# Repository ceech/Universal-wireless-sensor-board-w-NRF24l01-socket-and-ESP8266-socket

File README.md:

# Universal-wireless-sensor-board-w-NRF24l01-socket-and-ESP8266-socket
These are the CadsoftEagle board and schematic files. Link to the schematic:
http://s1164.photobucket.com/user/ceech123/media/DbALMmf_zpsipenpm1w.png.html

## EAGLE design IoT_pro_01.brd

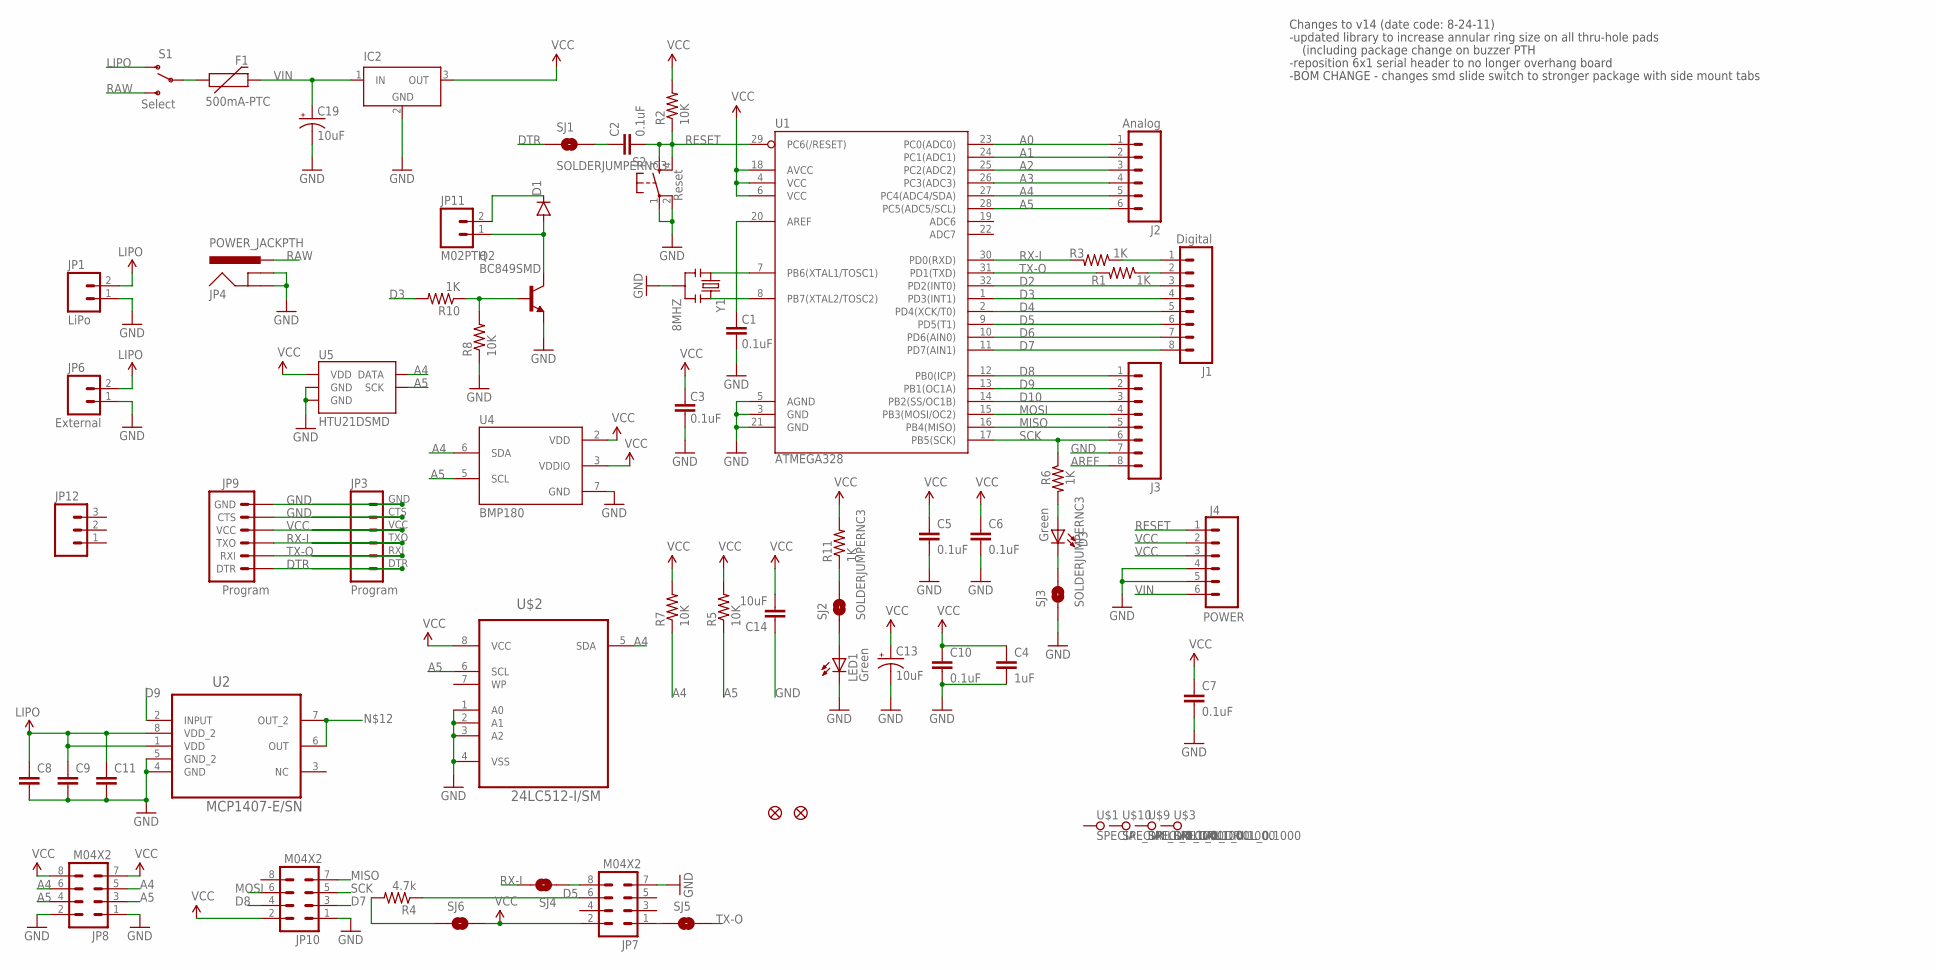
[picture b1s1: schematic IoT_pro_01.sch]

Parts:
C1, C2, C3, C5, C6, C7, C10: 0.1uF; 0805
C4: 1uF; 0805
C8, C9, C11: CAP0805; 0805
C13, C19: 10uF; EIA3216
C14: 10uF; 0805
D1: DIODESOD; SOD-323
D3: Green; PLCC2
F1: 500mA-PTC; PTC-1206
IC2: LT1129CST5; SOT223
J1: Digital; 1X08
J2: Analog; 1X06
J3: M081X08; 1X08
J4: POWER; 1X06
JP1: LiPo; MOLEX-1X2
JP2, JP5: FIDUCIAL1X2.5; FIDUCIAL-1X2.5
JP3: Program; 1X06
JP4: POWER_JACKPTH; POWER_JACK_PTH
JP6: External; 1X02
JP7, JP8, JP10: M04X2; 2X4
JP9: Program; 1X06-SMD
JP11: M02PTH; 1X02
JP12: M03PTH; 1X03
LED1: Green; PLCC2
Q2: BC849SMD; SOT23-BEC
R1, R3, R6, R10, R11: 1K; 0805
R2, R5, R7, R8: 10K; 0805
R4: 4.7k; 0805
S1: Select; SWITCH-SPST-SMD-A
S2: Reset; TACTILE_SWITCH_SMD
SJ1, SJ2, SJ3: SOLDERJUMPERNC3; SJ_2S-NOTRACE
SJ4, SJ5, SJ6: SOLDERJUMPERNC2; SJ_2S-NOTRACE
U1: ATMEGA328; TQFP32-08
U2: MCP1407-E/SN; SOIC127P600X175-8N
U4: BMP180
U5: HTU21DSMD; HTU21D
U$1, U$3, U$9, U$10: SPECIAL_DRILL_0.1000; PAD_0.1000
U$2: 24LC512-I/SM; SOIC127P794X203-8N
Y1: 8MHZ; RESONATOR-SMD

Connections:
3.3V: C8.1, C9.1, C11.1, JP6.2, U2.1 (VDD), U2.8 (VDD_2)
A0: J2.1, U1.23 (PC0(ADC0))
A1: J2.2, U1.24 (PC1(ADC1))
A2: J2.3, U1.25 (PC2(ADC2))
A3: J2.4, U1.26 (PC3(ADC3))
A4: J2.5, JP8.5, JP8.6, R7.1, U1.27 (PC4(ADC4/SDA)), U4.6 (SDA), U5.DATA, U$2.5 (SDA)
A5: J2.6, JP8.3, JP8.4, R5.1, U1.28 (PC5(ADC5/SCL)), U4.5 (SCL), U5.SCK, U$2.6 (SCL)
AREF: C1.2, J3.8, U1.20 (AREF)
D2: J1.3, U1.32 (PD2(INT0))
D3: J1.4, R10.2, U1.1 (PD3(INT1))
D4: J1.5, U1.2 (PD4(XCK/T0))
D5: J1.6, JP7.6, R4.1, U1.9 (PD5(T1))
D6: J1.7, U1.10 (PD6(AIN0))
D7: J1.8, JP10.3, U1.11 (PD7(AIN1))
D8: J3.1, JP10.4, U1.12 (PB0(ICP))
D9: J3.2, U1.13 (PB1(OC1A)), U2.2 (INPUT)
D10: J3.3, U1.14 (PB2(SS/OC1B))
DTR: JP3.DTR (1), JP9.1 (DTR), SJ1.1
GND: C1.1, C3.1, C4.2, C5.2, C6.2, C7.2, C8.2, C9.2, C10.2, C11.2, C13.C (-), C14.1, C19.C (-), IC2.2 (GND), IC2.4 (GND), J3.7, J4.4, J4.5, JP1.1, JP3.CTS (5), JP3.GND (6), JP4.GND, JP4.GNDBREAK, JP6.1, JP7.7, JP8.1, JP8.2, JP9.5 (CTS), JP9.6 (GND), JP10.1, LED1.C, Q2.E, R8.1, S2.1, S2.2, SJ3.1, U1.3 (GND), U1.5 (AGND), U1.21 (GND), U2.4 (GND), U2.5 (GND_2), U4.7 (GND), U5.7 (GND), U5.GND, U$2.1 (A0), U$2.2 (A1), U$2.3 (A2), U$2.4 (VSS), Y1.2
LIPO: JP1.2, S1.1 (O)
MISO: J3.5, JP10.7, U1.16 (PB4(MISO))
MOSI: J3.4, JP10.6, U1.15 (PB3(MOSI/OC2))
unnamed: C2.1, SJ1.2
unnamed: U1.7 (PB6(XTAL1/TOSC1)), Y1.1
unnamed: U1.8 (PB7(XTAL2/TOSC2)), Y1.3
unnamed: LED1.A, SJ2.1
unnamed: D3.A, R6.2
unnamed: R11.1, SJ2.2
unnamed: D3.C, SJ3.2
unnamed: JP7.8, SJ4.1
unnamed: JP7.1, SJ5.1
unnamed: D1.A, JP11.1, Q2.C, U2.6 (OUT), U2.7 (OUT_2)
unnamed: D1.C, JP11.2
unnamed: Q2.B, R8.2, R10.1
unnamed: R4.2, SJ6.1
unnamed: F1.1, S1.2
RAW: JP4.PWR, S1.3 (S)
RESET: C2.2, J4.1, R2.1, S2.3, S2.4, U1.29 (PC6(/RESET))
RX-I: JP3.TXO (3), JP9.3 (TXO), R3.2, SJ4.2, U1.30 (PD0(RXD))
RX-IP: J1.2, R1.1
SCK: J3.6, JP10.5, R6.1, U1.17 (PB5(SCK))
TX-O: JP3.RXI (2), JP9.2 (RXI), R1.2, SJ5.2, U1.31 (PD1(TXD))
TX-OP: J1.1, R3.1
VCC: C3.2, C4.1, C5.1, C6.1, C7.1, C10.1, C13.A (+), C14.2, IC2.3 (OUT), J4.2, J4.3, JP3.VCC (4), JP7.2, JP8.7, JP8.8, JP9.4 (VCC), JP10.2, R2.2, R5.2, R7.2, R11.2, SJ6.2, U1.4 (VCC), U1.6 (VCC), U1.18 (AVCC), U4.2 (VDD), U4.3 (VDDIO), U5.VDD, U$2.8 (VCC)
VIN: C19.A (+), F1.2, IC2.1 (IN), J4.6

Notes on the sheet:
Changes to v14 (date code: 8-24-11)
-updated library to increase annular ring size on all thru-hole pads
-reposition 6x1 serial header to no longer overhang board
-BOM CHANGE - changes smd slide switch to stronger package with side mount tabs
(including package change on buzzer PTH

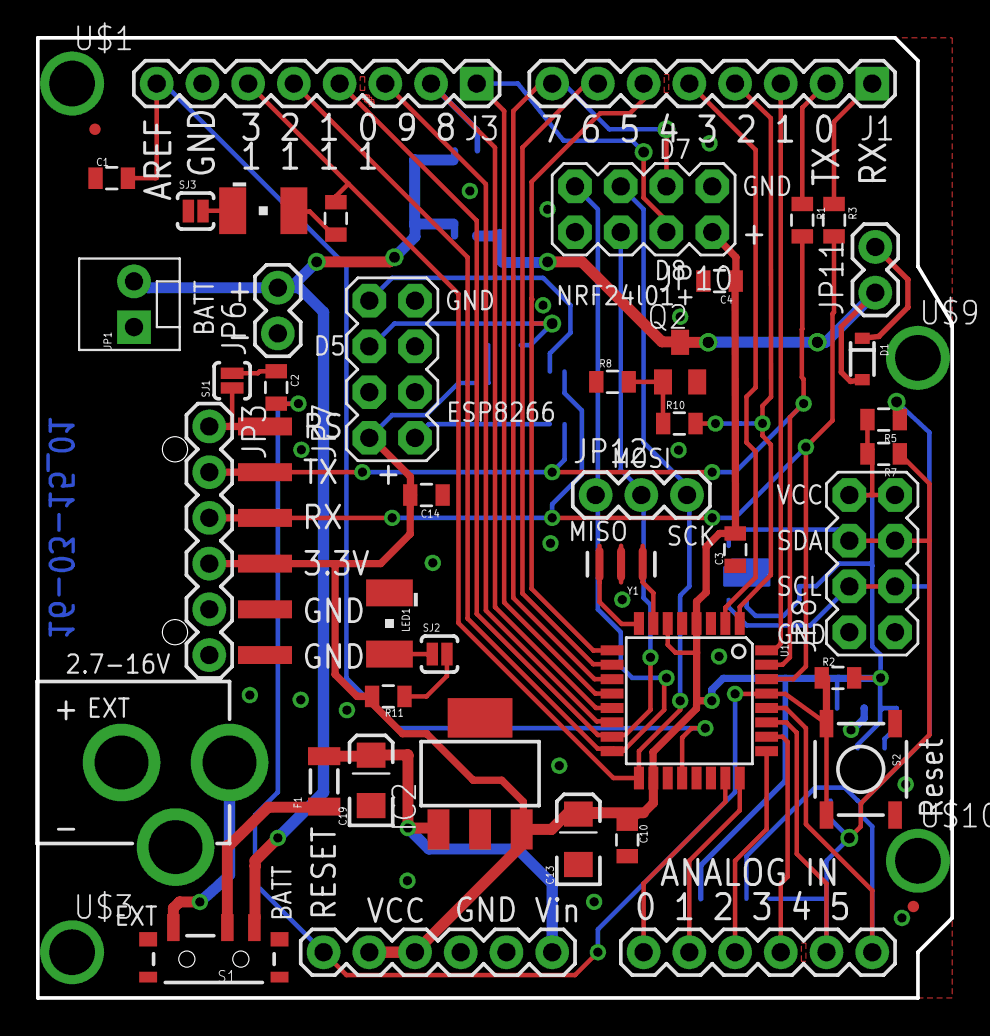
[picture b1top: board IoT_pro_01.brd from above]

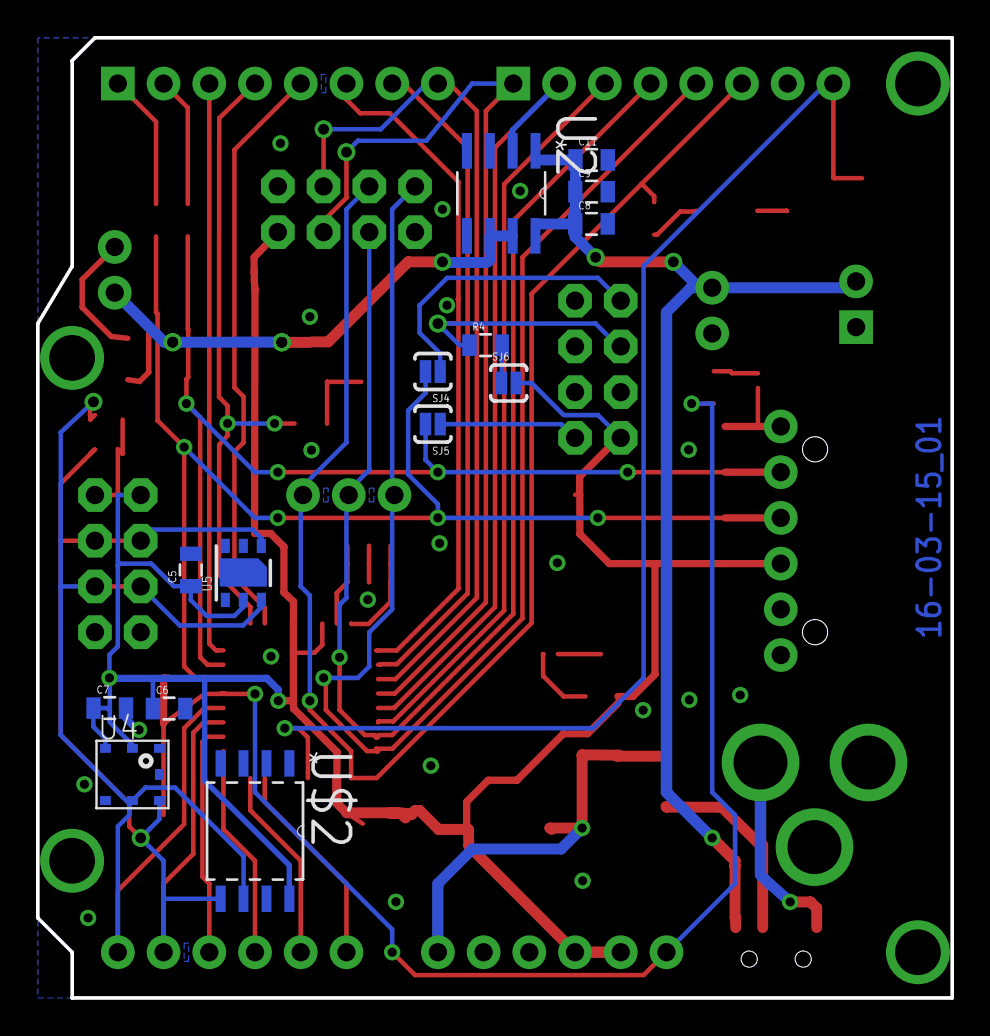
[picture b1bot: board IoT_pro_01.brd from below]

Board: 2 copper layers, 50.8 x 53.3 mm, 64 parts (14 on the bottom side), 45 nets.

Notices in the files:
parts and their libraries:
SparkFun-Connectors: Licensing: Creative Commons ShareAlike 4.0 International - https://creativecommons.org/licenses/by-sa/4.0
